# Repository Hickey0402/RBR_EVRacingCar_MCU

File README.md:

This is a beginner project for me as a newbie in RBR Electronics team. (Let the amazing journey of engineering begin)

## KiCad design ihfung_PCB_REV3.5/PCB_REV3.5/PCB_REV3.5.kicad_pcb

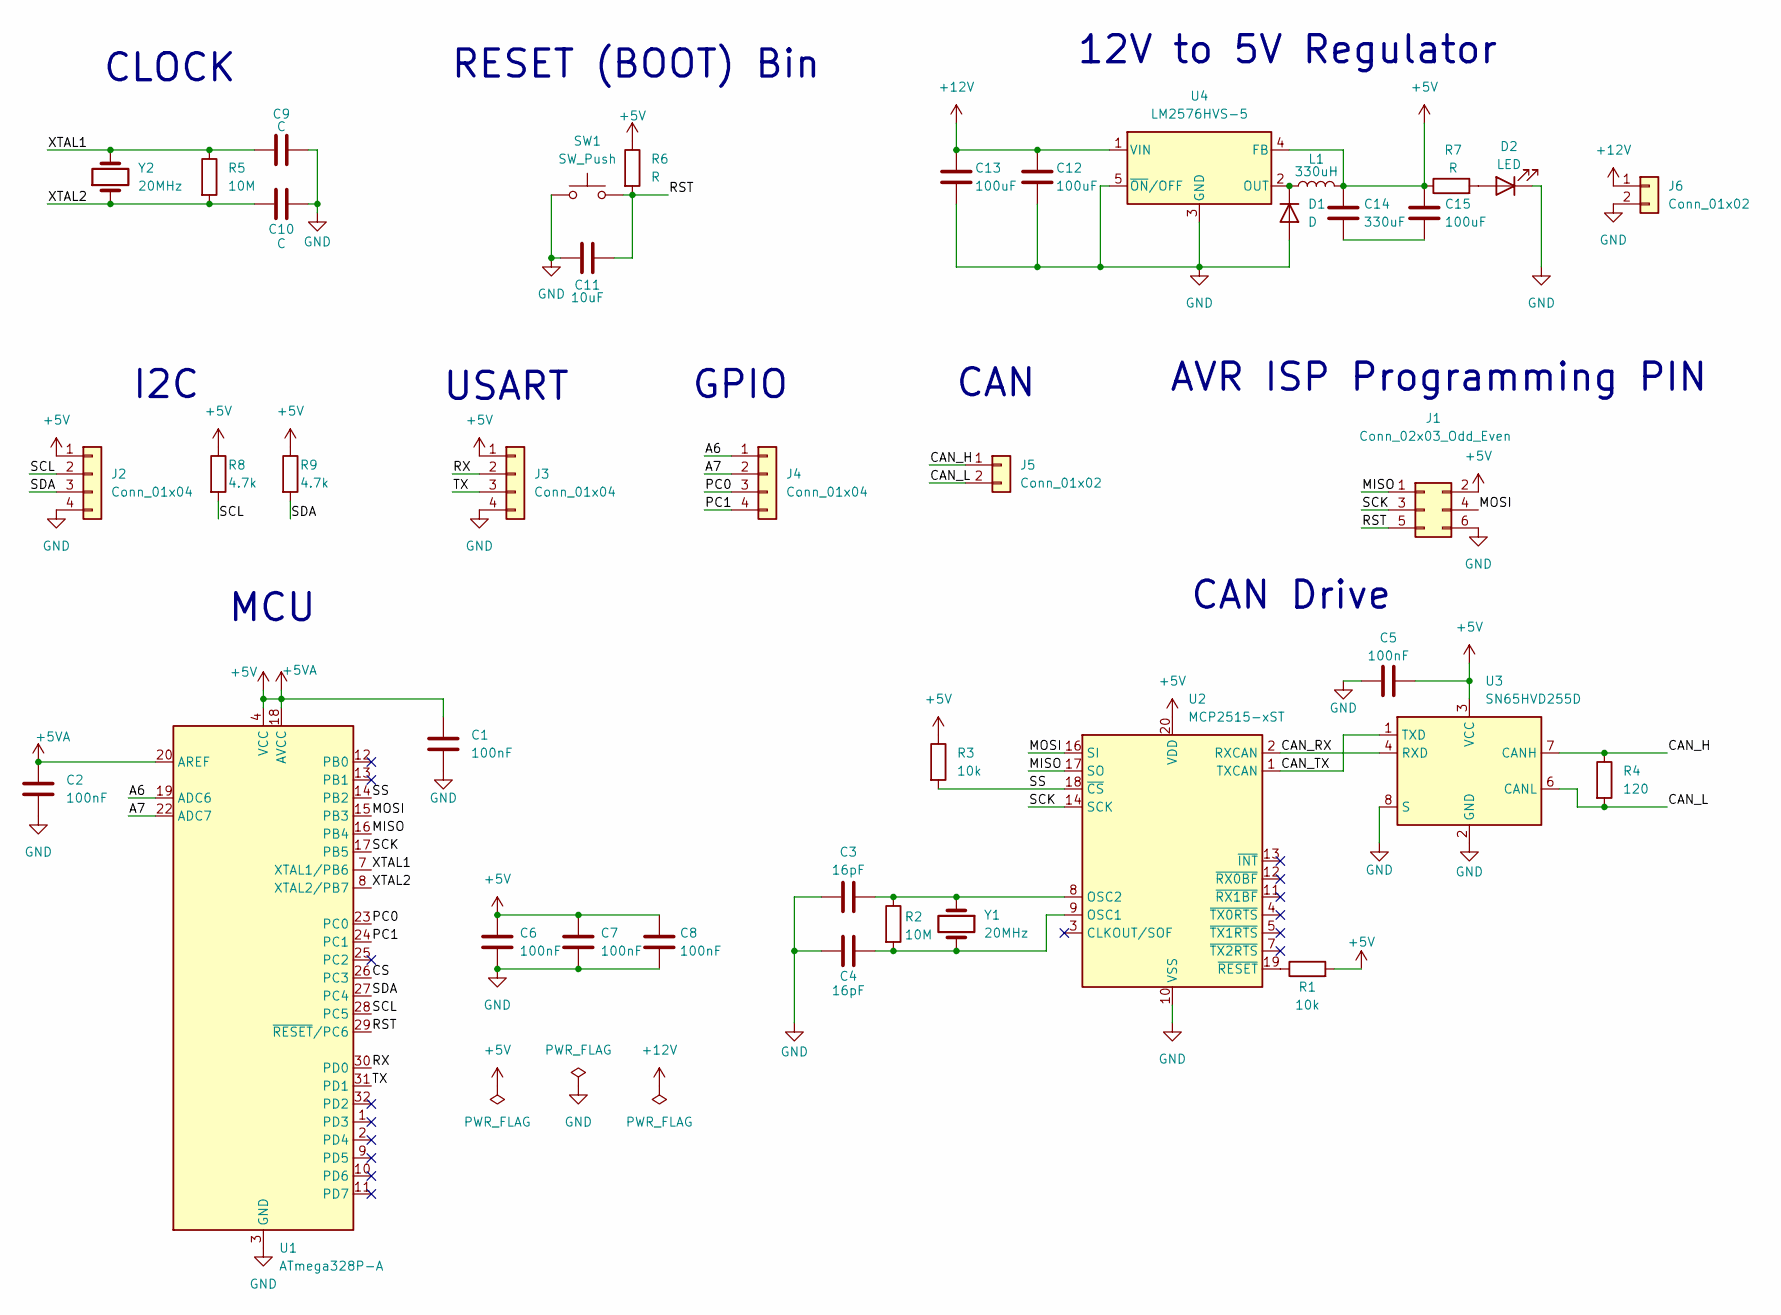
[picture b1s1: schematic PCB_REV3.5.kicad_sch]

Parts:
C1, C2, C5, C6, C7, C8: 100nF; CP_Elec_4x4.5
C3, C4: 16pF; CP_Elec_4x4.5
C9, C10: C; CP_Elec_4x4.5
C11: 10uF; CP_Elec_4x4.5
C12, C13, C15: 100uF; CP_Elec_4x4.5
C14: 330uF; CP_Elec_4x4.5
D1: D; D_0402_1005Metric
D2: LED; LED_0201_0603Metric
J1: Conn_02x03_Odd_Even; PinHeader_2x03_P1.00mm_Vertical
J2, J3, J4: Conn_01x04; PinHeader_1x04_P2.54mm_Vertical
J5, J6: Conn_01x02; PinHeader_1x02_P1.00mm_Vertical
L1: 330uH; L_Coilcraft_LPS4414
R1, R3: 10k; R_0201_0603Metric
R2, R5: 10M; R_0201_0603Metric
R4: 120; R_0201_0603Metric
R6, R7: R; R_0201_0603Metric
R8, R9: 4.7k; R_0201_0603Metric
SW1: SW_Push; SW_Push_1P1T_NO_CK_KSC6xxG
U1: ATmega328P-A; TQFP-32_7x7mm_P0.8mm
U2: MCP2515-xST; TSSOP-20_4.4x6.5mm_P0.65mm
U3: SN65HVD255D; SOIC-8_3.9x4.9mm_P1.27mm
U4: LM2576HVS-5; TO-263-5_TabPin3
Y1, Y2: 20MHz; Crystal_HC18-U_Vertical

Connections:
+5V: C1.1, C2.1, C5.2, C6.1, C7.1, C8.1, C14.1, C15.1, J1.2, J2.1, J3.1, L1.2, R1.2, R3.1, R6.1, R7.1, R8.1, R9.1, U1.4 (VCC), U1.6 (VCC), U1.18 (AVCC), U1.20 (AREF), U2.20 (VDD), U3.3 (VCC), U4.4 (FB)
+12V: C12.1, C13.1, J6.1, U4.1 (VIN)
/A6: J4.1, U1.19 (ADC6)
/A7: J4.2, U1.22 (ADC7)
/CAN_H: J5.1, R4.1, U3.7 (CANH)
/CAN_L: J5.2, R4.2, U3.6 (CANL)
/CAN_RX: U2.2 (RXCAN), U3.4 (RXD)
/CAN_TX: U2.1 (TXCAN), U3.1 (TXD)
/CS: U1.26 (PC3)
/MISO: J1.1, U1.16 (PB4), U2.17 (SO)
/MOSI: J1.4, U1.15 (PB3), U2.16 (SI)
/PC0: J4.3, U1.23 (PC0)
/PC1: J4.4, U1.24 (PC1)
/RST: C11.2, J1.5, R6.2, SW1.2, U1.29 (~RESET/PC6)
/RX: J3.2, U1.30 (PD0)
/SCK: J1.3, U1.17 (PB5), U2.14 (SCK)
/SCL: J2.2, R8.2, U1.28 (PC5)
/SDA: J2.3, R9.2, U1.27 (PC4)
/SS: R3.2, U1.14 (PB2), U2.18 (~CS)
/TX: J3.3, U1.31 (PD1)
/XTAL1: C9.1, R5.1, U1.7 (XTAL1/PB6), Y2.2
/XTAL2: C10.1, R5.2, U1.8 (XTAL2/PB7), Y2.1
GND: C1.2, C2.2, C3.1, C4.1, C5.1, C6.2, C7.2, C8.2, C9.2, C10.2, C11.1, C12.2, C13.2, D1.2 (A), D2.1 (K), J1.6, J2.4, J3.4, J6.2, SW1.1, U1.3 (GND), U1.5 (GND), U1.21 (GND), U2.10 (VSS), U3.2 (GND), U3.8 (S), U4.3 (GND), U4.5 (~ON/OFF)
unnamed: C14.2, C15.2
unnamed: D1.1 (K), L1.1, U4.2 (OUT)
unnamed: D2.2 (A), R7.2
unnamed: C4.2, R2.2, U2.9 (OSC1), Y1.2
unnamed: C3.2, R2.1, U2.8 (OSC2), Y1.1
unnamed: R1.1, U2.19 (~RESET)

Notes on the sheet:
I2C
12V to 5V Regulator
CLOCK
RESET (BOOT) Bin
USART
GPIO
AVR ISP Programming PIN
CAN Drive
MCU
CAN

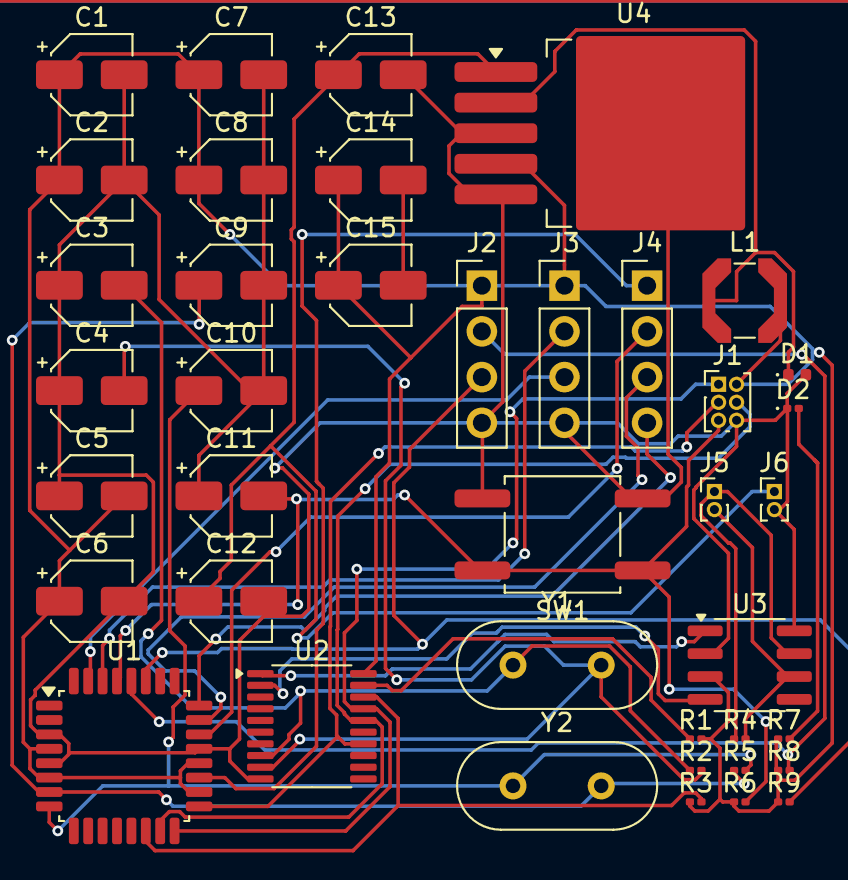
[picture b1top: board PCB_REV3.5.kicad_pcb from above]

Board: 2 copper layers, 40 parts (0 on the bottom side), 28 nets.
